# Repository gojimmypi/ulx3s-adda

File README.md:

# ULX3S-ADDA

https://github.com/albertxie/iverilog-tutorial

https://www.csee.umbc.edu/portal/help/VHDL/verilog/summary_one.html#specify

https://github.com/YosysHQ/nextpnr/blob/master/docs/constraints.md

http://www.latticesemi.com/-/media/LatticeSemi/Documents/ApplicationNotes/PT/sysIOUsageGuidelinesforLatticeDevices.ashx?document_id=3469

https://www.latticesemi.com/-/media/LatticeSemi/Documents/UserManuals/1D/design_planning_document.ashx?document_id=45589

	// 14ns after edge, data is stable (we'll use 16ns)
	specify 
		(J2_AD_PORT => i_ad_port_value) = 16;
	endspecify

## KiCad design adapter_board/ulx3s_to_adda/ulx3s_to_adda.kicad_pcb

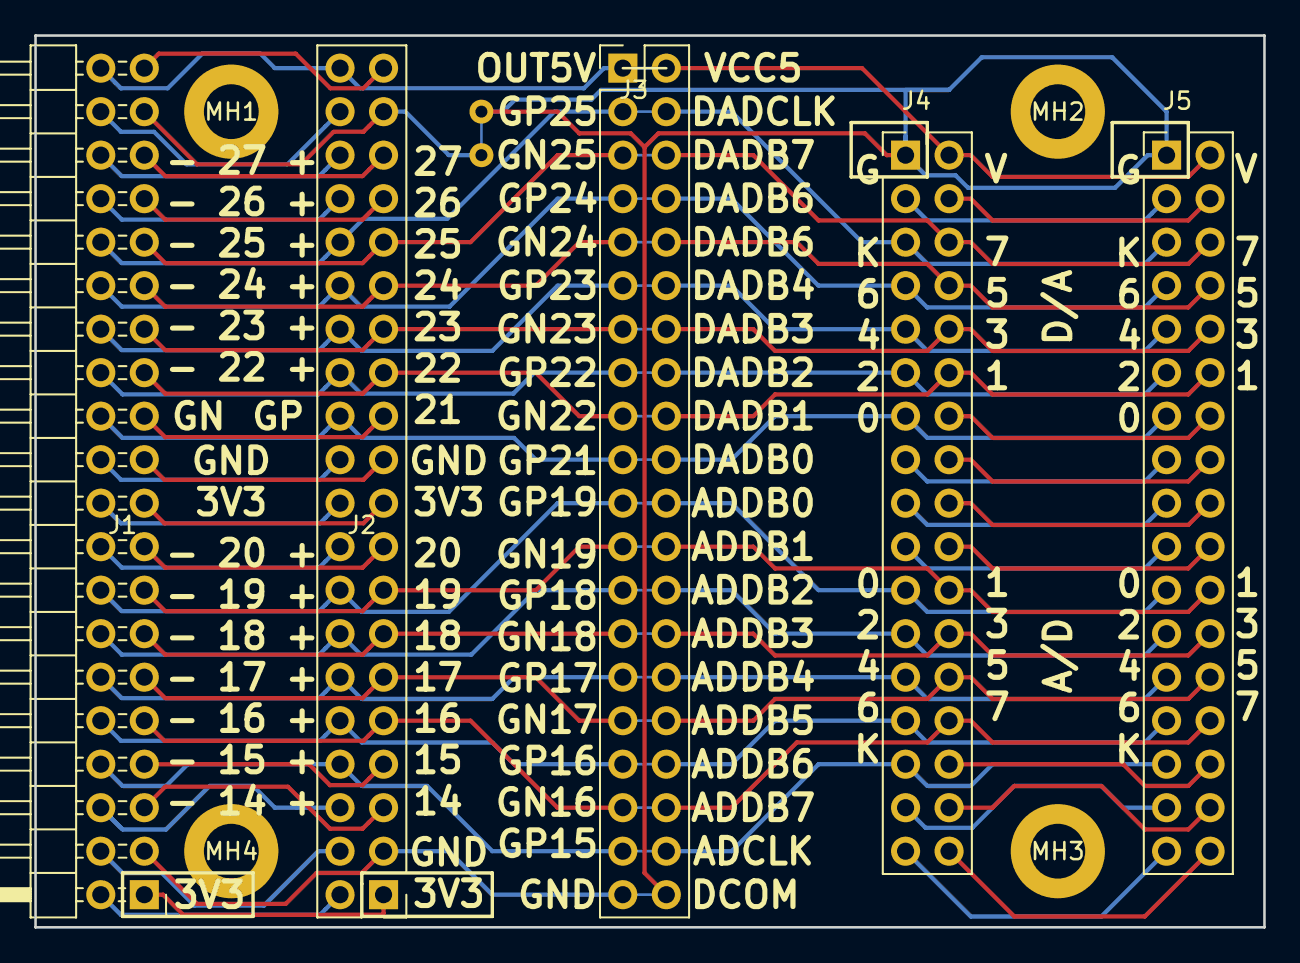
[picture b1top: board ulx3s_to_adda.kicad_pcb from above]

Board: 2 copper layers, 71.8 x 52.1 mm, 10 parts (0 on the bottom side), 74 nets.

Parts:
J1: ULX3S HEADER; PinHeader_2x20_P2.54mm_Horizontal
J2: ULX3S HEADER; PinHeader_2x20_P2.54mm_Vertical
J3: Conn_Dual_01x20_Male_Testpoint; PinHeader_1x20_Dual_P2.54mm_Vertical_TestPoint
J4, J5: Conn_02x17_Odd_Even; PinHeader_2x17_P2.54mm_Vertical
MH1, MH2, MH3, MH4: MountingHole; MountingHole_3.2mm_M3_ISO14580_Pad
R1: 0; PinHeader_Dual_1x2_P2.54mm_TestPoint.kicad_mod

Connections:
/3VP1: J1.1, J2.1
/3VP2: J1.2, J2.2
/3VP19: J1.19, J2.19
/3VP20: J1.20, J2.20
/ADCLK: J3.38, J4.29, J5.29
/ADDB0: J3.22, J4.21, J5.21
/ADDB1: J3.24, J4.22, J5.22
/ADDB2: J3.26, J4.23, J5.23
/ADDB3: J3.28, J4.24, J5.24
/ADDB4: J3.30, J4.25, J5.25
/ADDB5: J3.32, J4.26, J5.26
/ADDB6: J3.34, J4.27, J5.27
/ADDB7: J3.36, J4.28, J5.28
/DADB0: J3.20, J4.13, J5.13
/DADB1: J3.18, J4.12, J5.12
/DADB2: J3.16, J4.11, J5.11
/DADB3: J3.14, J4.10, J5.10
/DADB4: J3.12, J4.9, J5.9
/DADB5: J3.10, J4.8, J5.8
/DADB6: J3.8, J4.7, J5.7
/DADB7: J3.6, J4.6, J5.6
/DADCLK: J3.4, J4.5, J5.5
/DCOM: J3.40, J4.1, J5.1, R1.1
/GN14: J1.5, J2.5
/GN15: J1.7, J2.7
/GN16: J1.9, J2.9, J3.35
/GN17: J1.11, J2.11, J3.31
/GN18: J1.13, J2.13, J3.27
/GN19: J1.15, J2.15, J3.23
/GN20: J1.17, J2.17
/GN21: J1.23, J2.23
/GN22: J1.25, J2.25, J3.17
/GN23: J1.27, J2.27, J3.13
/GN24: J1.29, J2.29, J3.9
/GN25: J1.31, J2.31, J3.5
/GN26: J1.33, J2.33
/GN27: J1.35, J2.35
/GND3: J1.3, J2.3, J3.39
/GND4: J1.4, J2.4
/GND21: J1.21, J2.21
/GND22: J1.22, J2.22
/GND37: J1.37, J2.37, R1.2
/GND38: J1.38, J2.38
/GP14: J1.6, J2.6
/GP15: J1.8, J2.8, J3.37
/GP16: J1.10, J2.10, J3.33
/GP17: J1.12, J2.12, J3.29
/GP18: J1.14, J2.14, J3.25
/GP19: J1.16, J2.16, J3.21
/GP20: J1.18, J2.18
/GP21: J1.24, J2.24, J3.19
/GP22: J1.26, J2.26, J3.15
/GP23: J1.28, J2.28, J3.11
/GP24: J1.30, J2.30, J3.7
/GP25: J1.32, J2.32, J3.3
/GP26: J1.34, J2.34
/GP27: J1.36, J2.36
/IN5V: J1.39, J2.39
/NC3: J4.3, J5.3
/NC4: J4.4, J5.4
/NC14: J4.14, J5.14
/NC15: J4.15, J5.15
/NC16: J4.16, J5.16
/NC17: J4.17, J5.17
/NC18: J4.18, J5.18
/NC19: J4.19, J5.19
/NC20: J4.20, J5.20
/NC30: J4.30, J5.30
/NC31: J4.31, J5.31
/NC32: J4.32, J5.32
/NC33: J4.33, J5.33
/NC34: J4.34, J5.34
/OUT5V: J1.40, J2.40, J3.1
/VCC5: J3.2, J4.2, J5.2

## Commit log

2019-03-15 initial code
2019-03-16 attempt #2
2019-03-16 constraint file edits
2019-03-16 relabel as J2_AD_PORT
2019-03-16 revised connector, add AD/DA CLK
2019-03-16 non-working, pre-swap of P/N
2019-03-16 working AD
2019-03-16 add docs
2019-03-16 intial working AD! :)
2019-03-16 add ribbon cable connection pics
2019-03-18 default landscape & text searchable schematic
2019-03-18 programming w/ujprog; log file cleanup
2019-03-18 Updated J2 ULX3S Header w/ADDA pin notation
2019-03-18 AD/DA constraint revisions to apply
2019-03-18 completed AD/DA pin notation
2019-03-19 hacked, messy, but working end-to-end
2019-03-19 renamed from ulx3s-adda
2019-03-19 updated schematic from emard 8794fd1
2019-03-19 use other SYSCONFIG
2019-03-19 for reference only; renamed to ulx3s_adda
2019-03-19 initial verilator files (non-working)
2019-03-19 more verilatorr edits (non-working)
2019-03-19 renamed to use underscore rather than dash
2019-03-22 some iverilog files
2019-03-24 XWindows gtkwave WSL simulation support
2019-03-24 renamed to ulx3s_adda to avoid dash in name
2019-03-24 parameterize sim rm of vcd file
2019-03-24 basic functionality working with gtkwave
2019-03-24 no need to save vvp files with project
2019-04-01 V1.0 of ULX3S to AD/DA Adapter PCB
2019-04-10 cleaned up, added Makefile toolchain install
2019-04-10 $(PROJ)_out.config not [.out]
2019-04-11 DOS username rather than WSL for XWindows copy
2019-04-11 properly export DISPLAY=:0; in spawned process
2019-04-11 code cleanup. test benches now operational
2019-04-11 update toolchain git clone path
2019-04-12 multi-line spawn of gtkwave needs line extension chars
2019-04-12 multi-line cal lto gtkwave for readability
2019-04-12 check if ULX3S_WSL_Toolchain is alreaddy installed
2019-04-12 include ULX3S_WSL_Toolchain gist as submodule
